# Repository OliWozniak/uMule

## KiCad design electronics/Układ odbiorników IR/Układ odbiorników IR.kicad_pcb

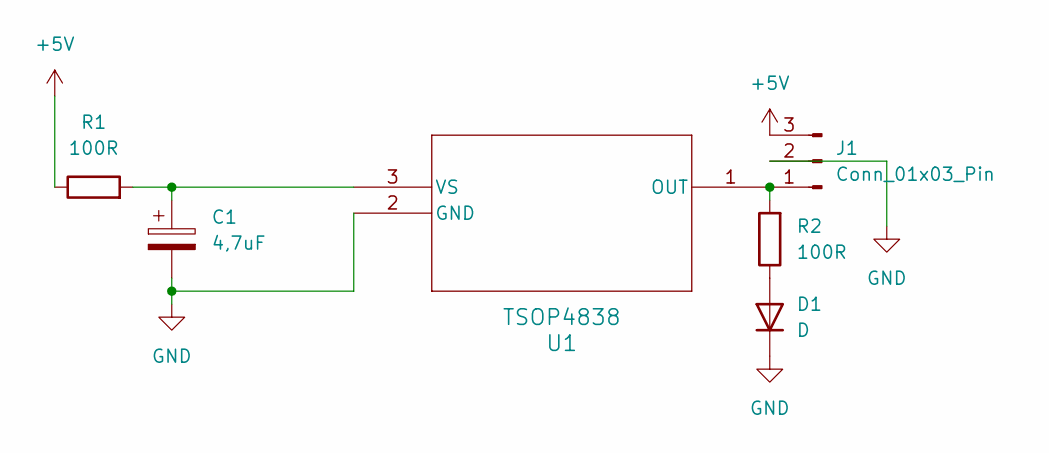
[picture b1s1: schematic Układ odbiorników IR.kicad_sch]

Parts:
C1: 4,7uF; C_0805_2012Metric_Pad1.18x1.45mm_HandSolder
D1: D; LED_0603_1608Metric
J1: Conn_01x03_Pin; PinHeader_1x03_P2.54mm_Vertical
R1, R2: 100R; R_0603_1608Metric_Pad0.98x0.95mm_HandSolder
U1: TSOP4838; TSOP48_VIS

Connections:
+5V: J1.3, R1.1
GND: C1.2, D1.1 (K), J1.2, U1.2 (GND)
unnamed: D1.2 (A), R2.1
unnamed: J1.1, R2.2, U1.1 (OUT)
unnamed: C1.1, R1.2, U1.3 (VS)

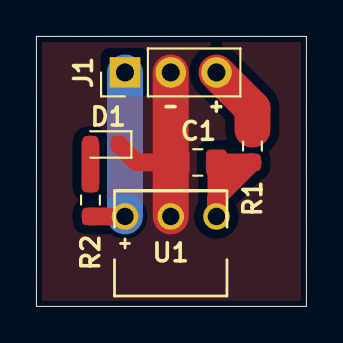
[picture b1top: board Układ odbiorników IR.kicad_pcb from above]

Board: 2 copper layers, 15.0 x 15.0 mm, 6 parts (0 on the bottom side), 5 nets.

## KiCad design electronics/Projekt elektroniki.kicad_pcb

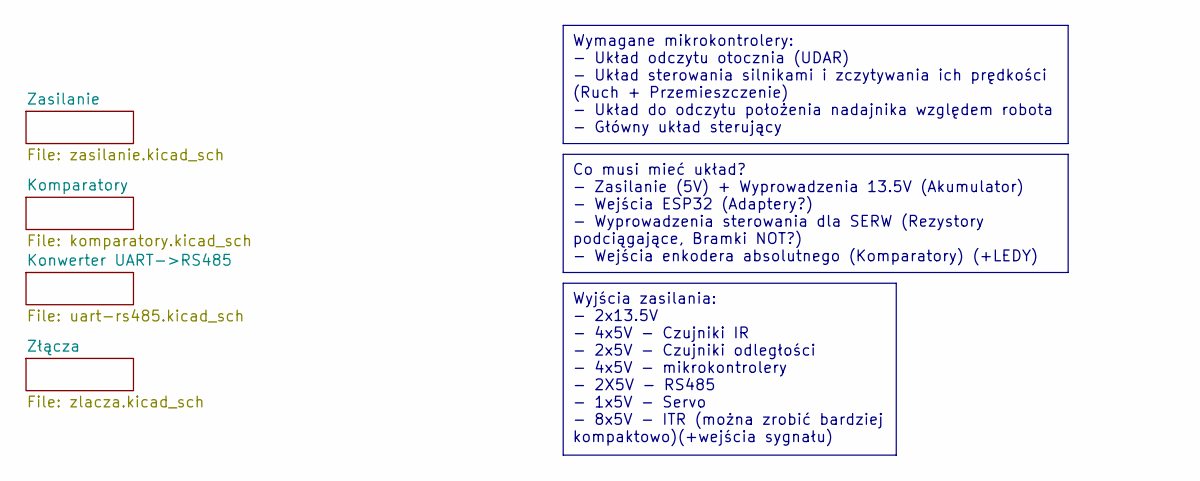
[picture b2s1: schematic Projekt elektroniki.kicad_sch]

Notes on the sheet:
Wyjścia zasilania: - 2x13.5V - 4x5V - Czujniki IR - 2x5V - Czujniki odległości - 4x5V - mikrokontrolery - 2X5V - RS485 - 1x5V - Servo - 8x5V - ITR (można zrobić bardziej kompaktowo)(+wejścia sygnału)
Wymagane mikrokontrolery: - Układ odczytu otocznia (UDAR) - Układ sterowania silnikami i zczytywania ich prędkości (Ruch + Przemieszczenie) - Układ do odczytu położenia nadajnika względem robota - Główny układ sterujący
Co musi mieć układ? - Zasilanie (5V) + Wyprowadzenia 13.5V (Akumulator) - Wejścia ESP32 (Adaptery?) - Wyprowadzenia sterowania dla SERW (Rezystory podciągające, Bramki NOT?) - Wejścia enkodera absolutnego (Komparatory) (+LEDY)

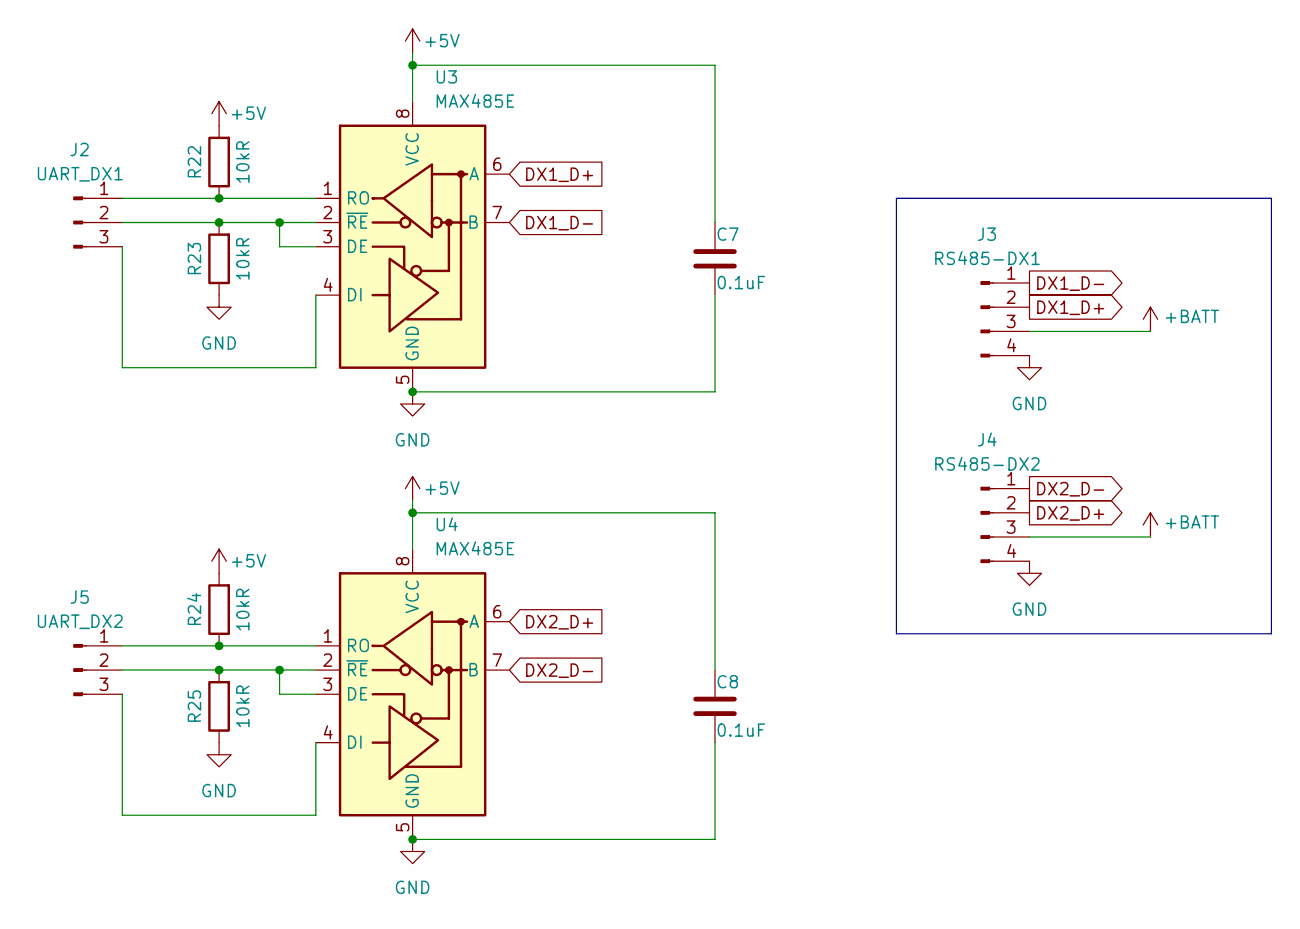
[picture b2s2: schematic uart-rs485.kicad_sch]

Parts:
C7, C8: 0.1uF; C_0603_1608Metric
J2: UART_DX1; PinHeader_1x03_P2.54mm_Vertical
J3: RS485-DX1; Molex_SPOX_5267-04A_1x04_P2.50mm_Vertical
J4: RS485-DX2; Molex_SPOX_5267-04A_1x04_P2.50mm_Vertical
J5: UART_DX2; PinHeader_1x03_P2.54mm_Vertical
R22, R23, R24, R25: 10kR; R_0603_1608Metric_Pad0.98x0.95mm_HandSolder
U3, U4: MAX485E; SOIC127P600X175-8N (MAX485)

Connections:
+5V: C7.2, C8.2, R22.2, R24.2, U3.8 (VCC), U4.8 (VCC); also elsewhere on the board
DX1_D+: J3.2, U3.6 (A)
DX1_D-: J3.1, U3.7 (B)
DX2_D+: J4.2, U4.6 (A)
DX2_D-: J4.1, U4.7 (B)
GND: C7.1, C8.1, J3.4, J4.4, R23.1, R25.1, U3.5 (GND), U4.5 (GND); also elsewhere on the board
unnamed: J2.1, R22.1, U3.1 (RO)
unnamed: J2.2, R23.2, U3.2 (~RE), U3.3 (DE)
unnamed: J2.3, U3.4 (DI)
unnamed: J5.1, R24.1, U4.1 (RO)
unnamed: J5.2, R25.2, U4.2 (~RE), U4.3 (DE)
unnamed: J5.3, U4.4 (DI)
Przetwornica_VIN: J3.3, J4.3; also elsewhere on the board

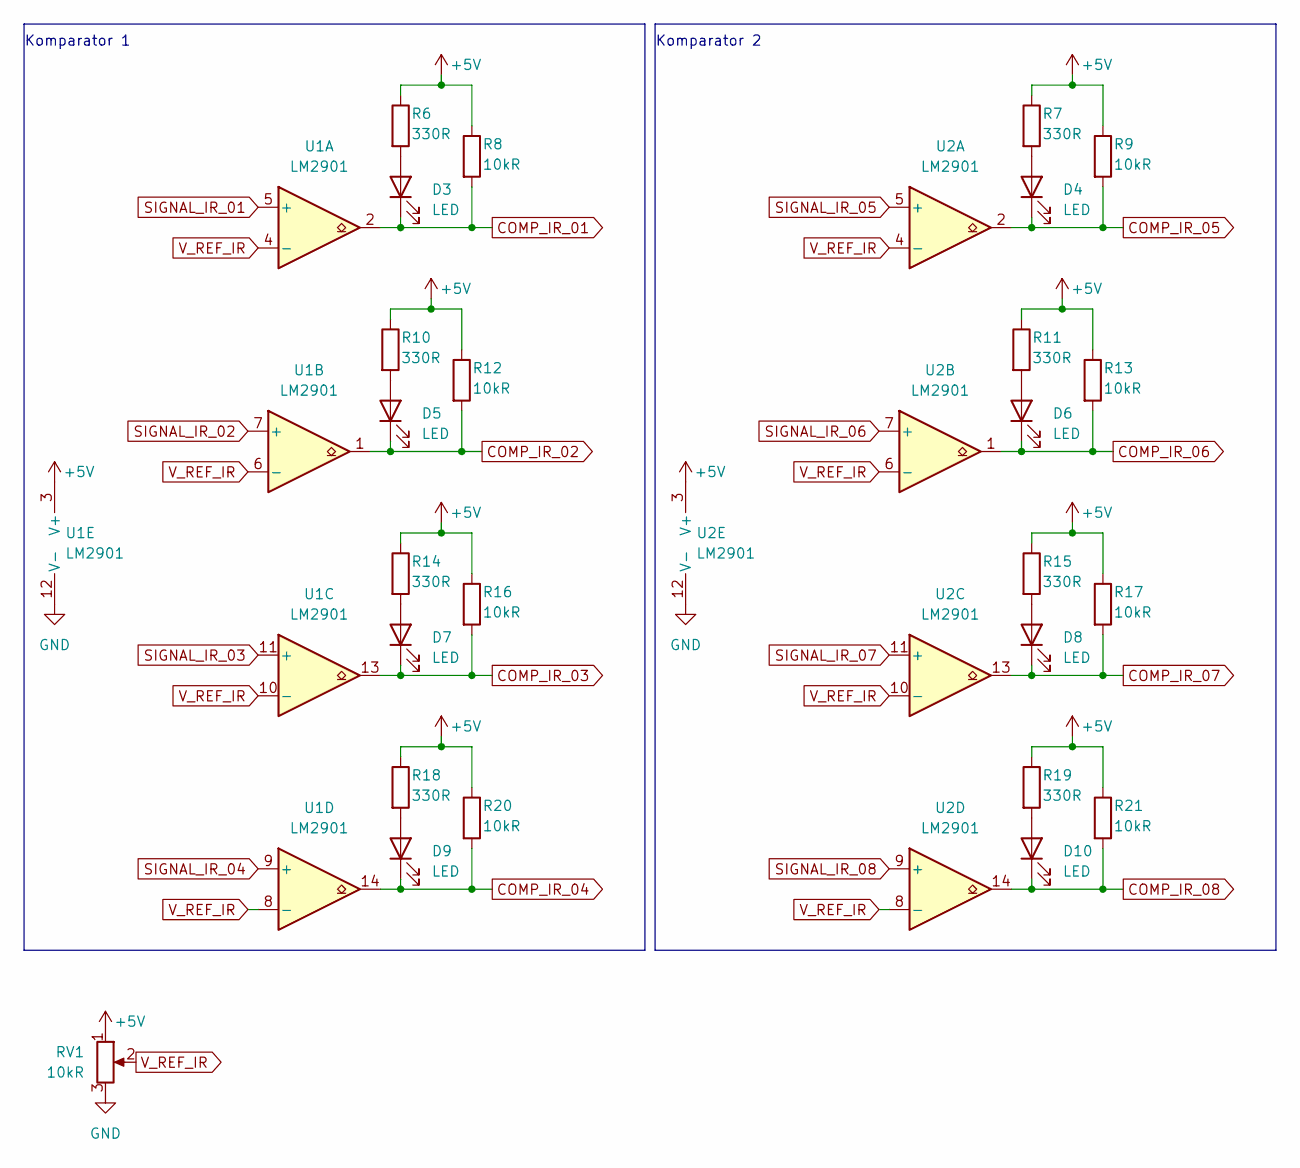
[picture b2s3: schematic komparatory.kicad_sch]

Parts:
D3, D4, D5, D6, D7, D8, D9, D10: LED; LED_0603_1608Metric_Pad1.05x0.95mm_HandSolder
R6, R7, R10, R11, R14, R15, R18, R19: 330R; R_0603_1608Metric_Pad0.98x0.95mm_HandSolder
R8, R9, R12, R13, R16, R17, R20, R21: 10kR; R_0603_1608Metric_Pad0.98x0.95mm_HandSolder
RV1: 10kR; Potencjometr 3,2x3,4
U1, U2: LM2901; SOIC127P600X175-14N

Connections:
+5V: R6.1, R7.1, R8.1, R9.1, R10.1, R11.1, R12.1, R13.1, R14.1, R15.1, R16.1, R17.1, R18.1, R19.1, R20.1, R21.1, RV1.1, U1.3 (V+), U2.3 (V+); also elsewhere on the board
COMP_IR_01: D3.1 (K), R8.2, U1.2; also elsewhere on the board
COMP_IR_02: D5.1 (K), R12.2, U1.1; also elsewhere on the board
COMP_IR_03: D7.1 (K), R16.2, U1.13; also elsewhere on the board
COMP_IR_04: D9.1 (K), R20.2, U1.14; also elsewhere on the board
COMP_IR_05: D4.1 (K), R9.2, U2.2; also elsewhere on the board
COMP_IR_06: D6.1 (K), R13.2, U2.1; also elsewhere on the board
COMP_IR_07: D8.1 (K), R17.2, U2.13; also elsewhere on the board
COMP_IR_08: D10.1 (K), R21.2, U2.14; also elsewhere on the board
GND: RV1.3, U1.12 (V-), U2.12 (V-); also elsewhere on the board
unnamed: D3.2 (A), R6.2
unnamed: D4.2 (A), R7.2
unnamed: D5.2 (A), R10.2
unnamed: D6.2 (A), R11.2
unnamed: D7.2 (A), R14.2
unnamed: D8.2 (A), R15.2
unnamed: D9.2 (A), R18.2
unnamed: D10.2 (A), R19.2
SIGNAL_IR_01: U1.5 (+); also elsewhere on the board
SIGNAL_IR_02: U1.7 (+); also elsewhere on the board
SIGNAL_IR_03: U1.11 (+); also elsewhere on the board
SIGNAL_IR_04: U1.9 (+); also elsewhere on the board
SIGNAL_IR_05: U2.5 (+); also elsewhere on the board
SIGNAL_IR_06: U2.7 (+); also elsewhere on the board
SIGNAL_IR_07: U2.11 (+); also elsewhere on the board
SIGNAL_IR_08: U2.9 (+); also elsewhere on the board
V_REF_IR: RV1.2, U1.4 (-), U1.6 (-), U1.8 (-), U1.10 (-), U2.4 (-), U2.6 (-), U2.8 (-), U2.10 (-)

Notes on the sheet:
Komparator 2
Komparator 1

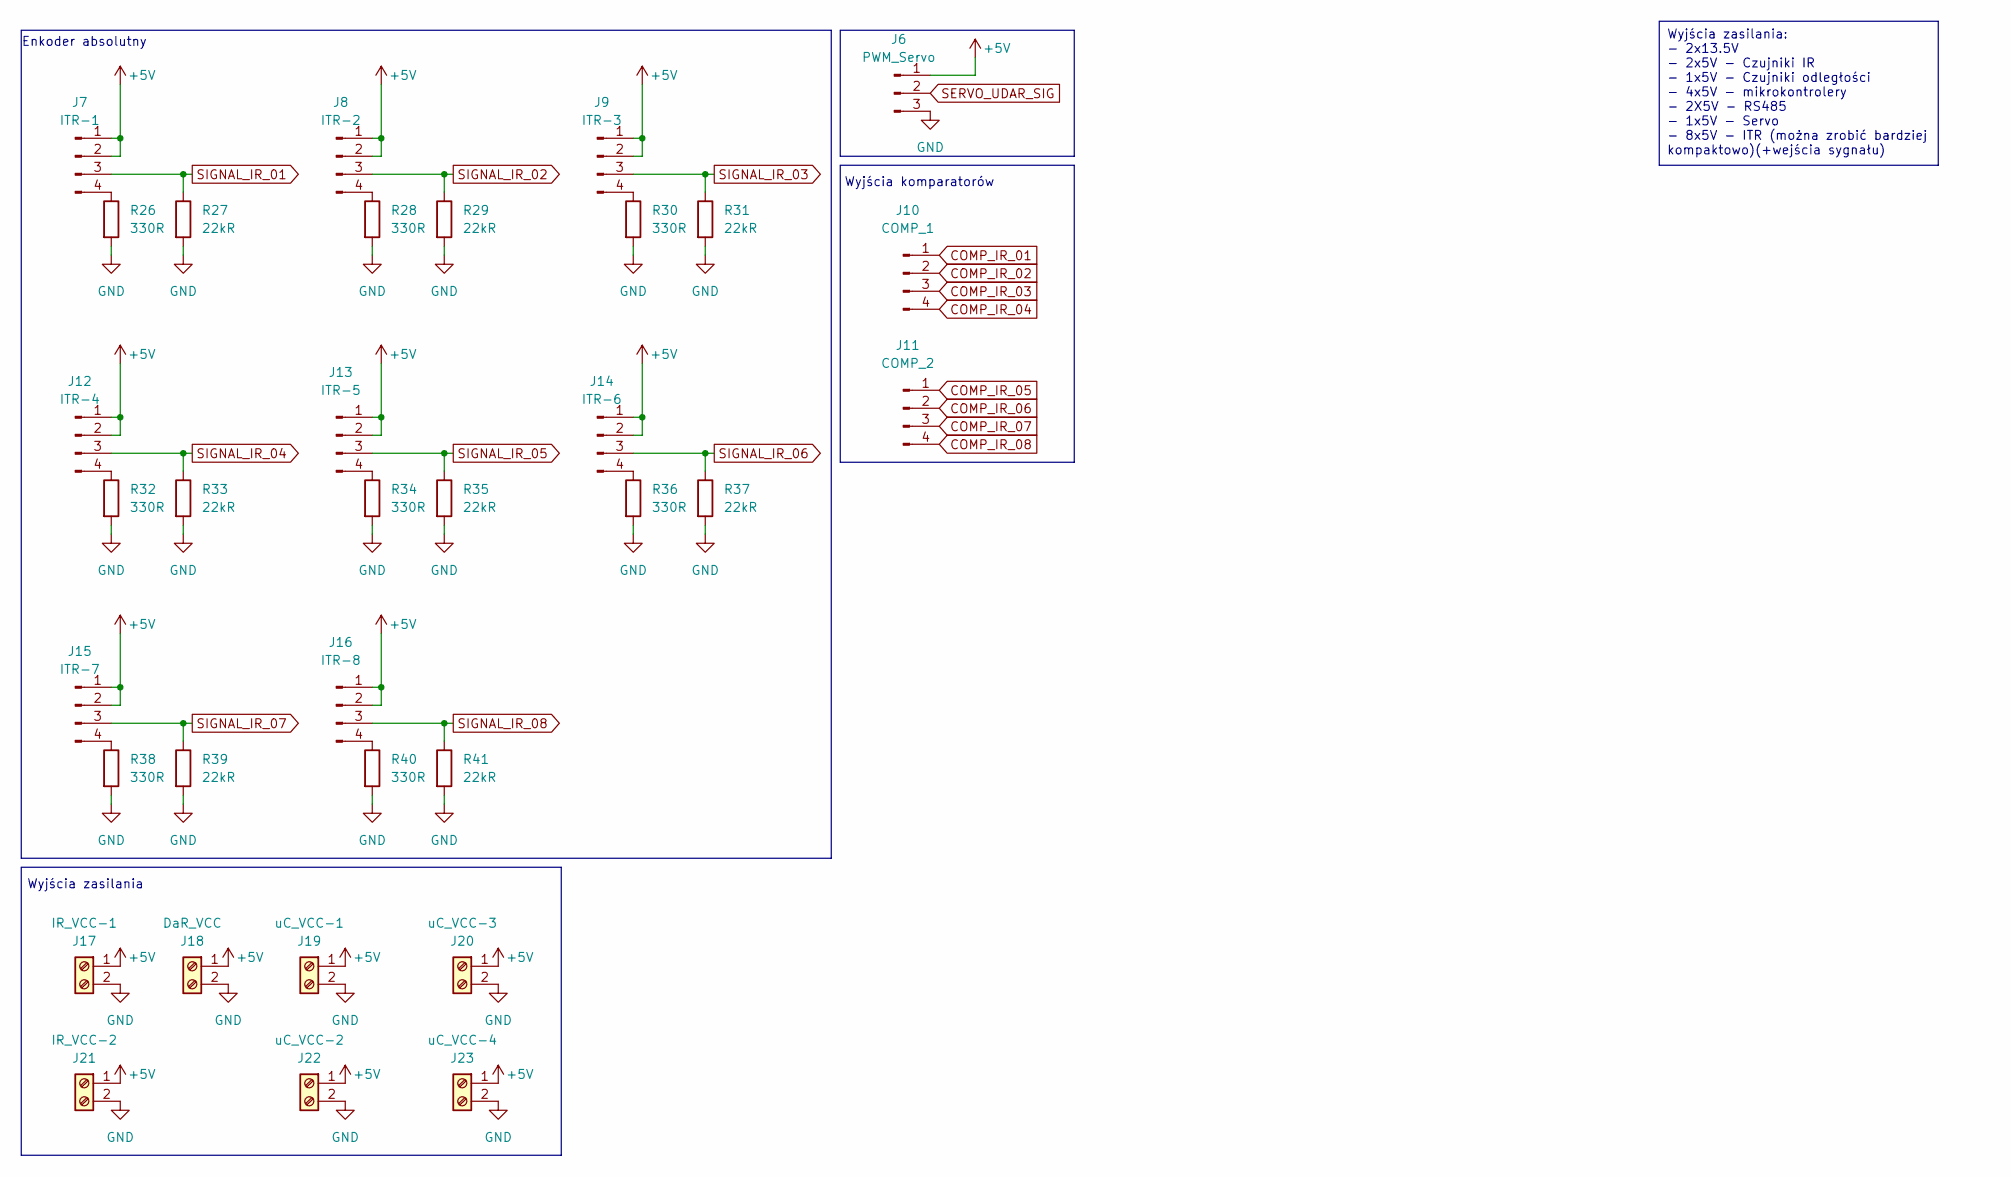
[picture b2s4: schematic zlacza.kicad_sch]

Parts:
J6: PWM_Servo; PinHeader_1x03_P2.54mm_Vertical
J7: ITR-1; Molex_SPOX_5267-04A_1x04_P2.50mm_Vertical
J8: ITR-2; Molex_SPOX_5267-04A_1x04_P2.50mm_Vertical
J9: ITR-3; Molex_SPOX_5267-04A_1x04_P2.50mm_Vertical
J10: COMP_1; Molex_SPOX_5267-04A_1x04_P2.50mm_Vertical
J11: COMP_2; Molex_SPOX_5267-04A_1x04_P2.50mm_Vertical
J12: ITR-4; Molex_SPOX_5267-04A_1x04_P2.50mm_Vertical
J13: ITR-5; Molex_SPOX_5267-04A_1x04_P2.50mm_Vertical
J14: ITR-6; Molex_SPOX_5267-04A_1x04_P2.50mm_Vertical
J15: ITR-7; Molex_SPOX_5267-04A_1x04_P2.50mm_Vertical
J16: ITR-8; Molex_SPOX_5267-04A_1x04_P2.50mm_Vertical
J17: IR_VCC-1; ARK 01x02 5mm
J18: DaR_VCC; ARK 01x02 5mm
J19: uC_VCC-1; ARK 01x02 5mm
J20: uC_VCC-3; ARK 01x02 5mm
J21: IR_VCC-2; ARK 01x02 5mm
J22: uC_VCC-2; ARK 01x02 5mm
J23: uC_VCC-4; ARK 01x02 5mm
R26, R28, R30, R32, R34, R36, R38, R40: 330R; R_0603_1608Metric_Pad0.98x0.95mm_HandSolder
R27, R29, R31, R33, R35, R37, R39, R41: 22kR; R_0603_1608Metric_Pad0.98x0.95mm_HandSolder

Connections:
+5V: J6.1, J7.1, J7.2, J8.1, J8.2, J9.1, J9.2, J12.1, J12.2, J13.1, J13.2, J14.1, J14.2, J15.1, J15.2, J16.1, J16.2, J17.1, J18.1, J19.1, J20.1, J21.1, J22.1, J23.1; also elsewhere on the board
COMP_IR_01: J10.1; also elsewhere on the board
COMP_IR_02: J10.2; also elsewhere on the board
COMP_IR_03: J10.3; also elsewhere on the board
COMP_IR_04: J10.4; also elsewhere on the board
COMP_IR_05: J11.1; also elsewhere on the board
COMP_IR_06: J11.2; also elsewhere on the board
COMP_IR_07: J11.3; also elsewhere on the board
COMP_IR_08: J11.4; also elsewhere on the board
GND: J6.3, J17.2, J18.2, J19.2, J20.2, J21.2, J22.2, J23.2, R26.2, R27.2, R28.2, R29.2, R30.2, R31.2, R32.2, R33.2, R34.2, R35.2, R36.2, R37.2, R38.2, R39.2, R40.2, R41.2; also elsewhere on the board
unnamed: J7.4, R26.1
unnamed: J8.4, R28.1
unnamed: J9.4, R30.1
unnamed: J12.4, R32.1
unnamed: J13.4, R34.1
unnamed: J14.4, R36.1
unnamed: J15.4, R38.1
unnamed: J16.4, R40.1
SERVO_UDAR_SIG: J6.2
SIGNAL_IR_01: J7.3, R27.1; also elsewhere on the board
SIGNAL_IR_02: J8.3, R29.1; also elsewhere on the board
SIGNAL_IR_03: J9.3, R31.1; also elsewhere on the board
SIGNAL_IR_04: J12.3, R33.1; also elsewhere on the board
SIGNAL_IR_05: J13.3, R35.1; also elsewhere on the board
SIGNAL_IR_06: J14.3, R37.1; also elsewhere on the board
SIGNAL_IR_07: J15.3, R39.1; also elsewhere on the board
SIGNAL_IR_08: J16.3, R41.1; also elsewhere on the board

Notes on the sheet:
Wyjścia zasilania: - 2x13.5V - 2x5V - Czujniki IR - 1x5V - Czujniki odległości - 4x5V - mikrokontrolery - 2X5V - RS485 - 1x5V - Servo - 8x5V - ITR (można zrobić bardziej kompaktowo)(+wejścia sygnału)
Wyjścia zasilania
Wyjścia komparatorów
Enkoder absolutny

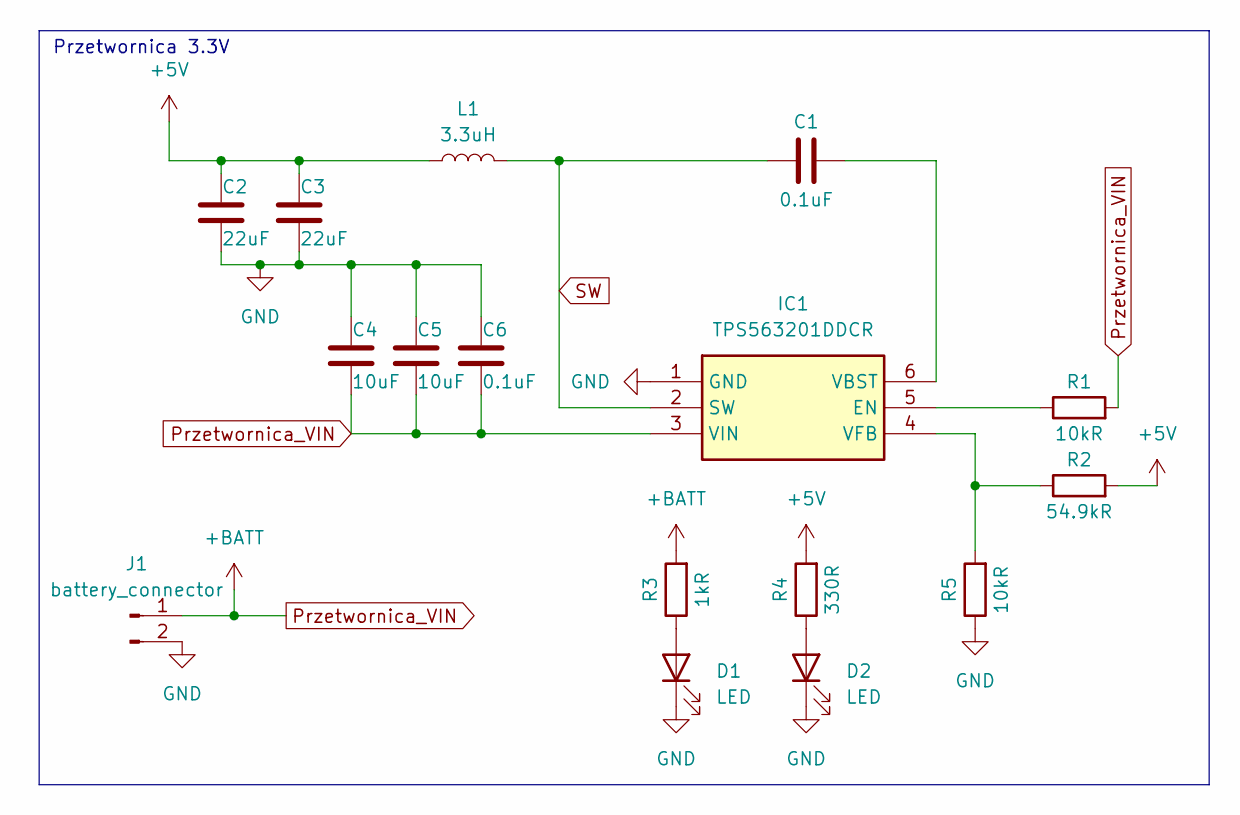
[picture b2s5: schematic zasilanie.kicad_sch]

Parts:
C1, C6: 0.1uF; C_0603_1608Metric
C2, C3: 22uF; C_0805_2012Metric
C4, C5: 10uF; C_0805_2012Metric
D1, D2: LED; LED_0603_1608Metric_Pad1.05x0.95mm_HandSolder
IC1: TPS563201DDCR; SOT95P280X110-6N; Manufacturer_Part_Number TPS563201DDCR
J1: battery_connector; ARK 01x02 5mm
L1: 3.3uH; L_Bourns_SRP7028A_7.3x6.6mm
R1, R5: 10kR; R_0603_1608Metric_Pad0.98x0.95mm_HandSolder
R2: 54.9kR; R_0603_1608Metric
R3: 1kR; R_0603_1608Metric
R4: 330R; R_0603_1608Metric_Pad0.98x0.95mm_HandSolder

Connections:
+5V: C2.2, C3.2, L1.1, R2.2, R4.2; also elsewhere on the board
GND: C2.1, C3.1, C4.2, C5.2, C6.2, D1.1 (K), D2.1 (K), IC1.1 (GND), J1.2, R5.1; also elsewhere on the board
unnamed: D1.2 (A), R3.1
unnamed: D2.2 (A), R4.1
unnamed: IC1.5 (EN), R1.1
unnamed: C1.2, IC1.6 (VBST)
unnamed: IC1.4 (VFB), R2.1, R5.2
Przetwornica_VIN: C4.1, C5.1, C6.1, IC1.3 (VIN), J1.1, R1.2, R3.2; also elsewhere on the board
SW: C1.1, IC1.2 (SW), L1.2

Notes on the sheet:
Przetwornica 3.3V

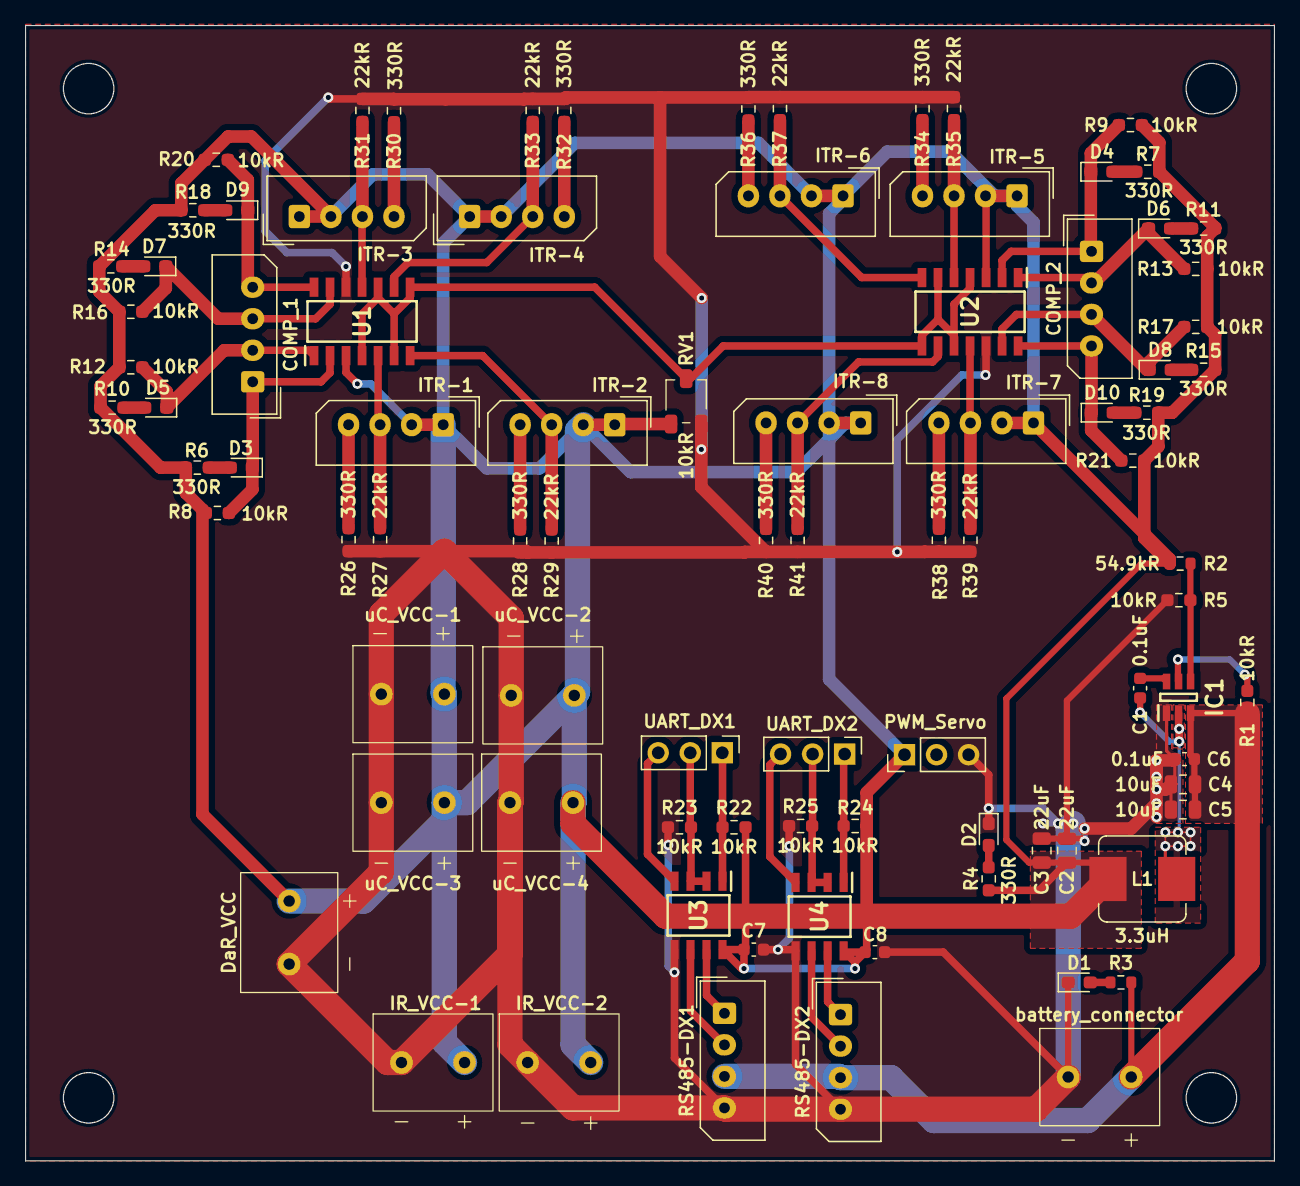
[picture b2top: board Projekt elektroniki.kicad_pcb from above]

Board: 2 copper layers, 99.0 x 89.9 mm, 89 parts (0 on the bottom side), 52 nets.

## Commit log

2024-11-24 initial commit
    Podstawowe schematy i projekty
2024-12-14 Dodano Schemat logiczny uMule.drawio
2024-12-15 Dodano Regulator_PD.drawio.pdf
2026-04-22 mechanics project cleanup
2026-04-22 file tree reorganisation
2026-04-22 Working base project. Ready to add modules
2026-04-22 Added current board (simplified model)
2026-05-02 added some attachments to 3d models
2026-05-04 most of attachments is ready. Sent to printing
2026-05-24 added ball caster and fixed model
2026-05-24 fixed model's orientation
